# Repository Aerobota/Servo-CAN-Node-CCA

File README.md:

# Servo-CAN-Node-CCA
Circuit Card Assembly for Servo CAN Node

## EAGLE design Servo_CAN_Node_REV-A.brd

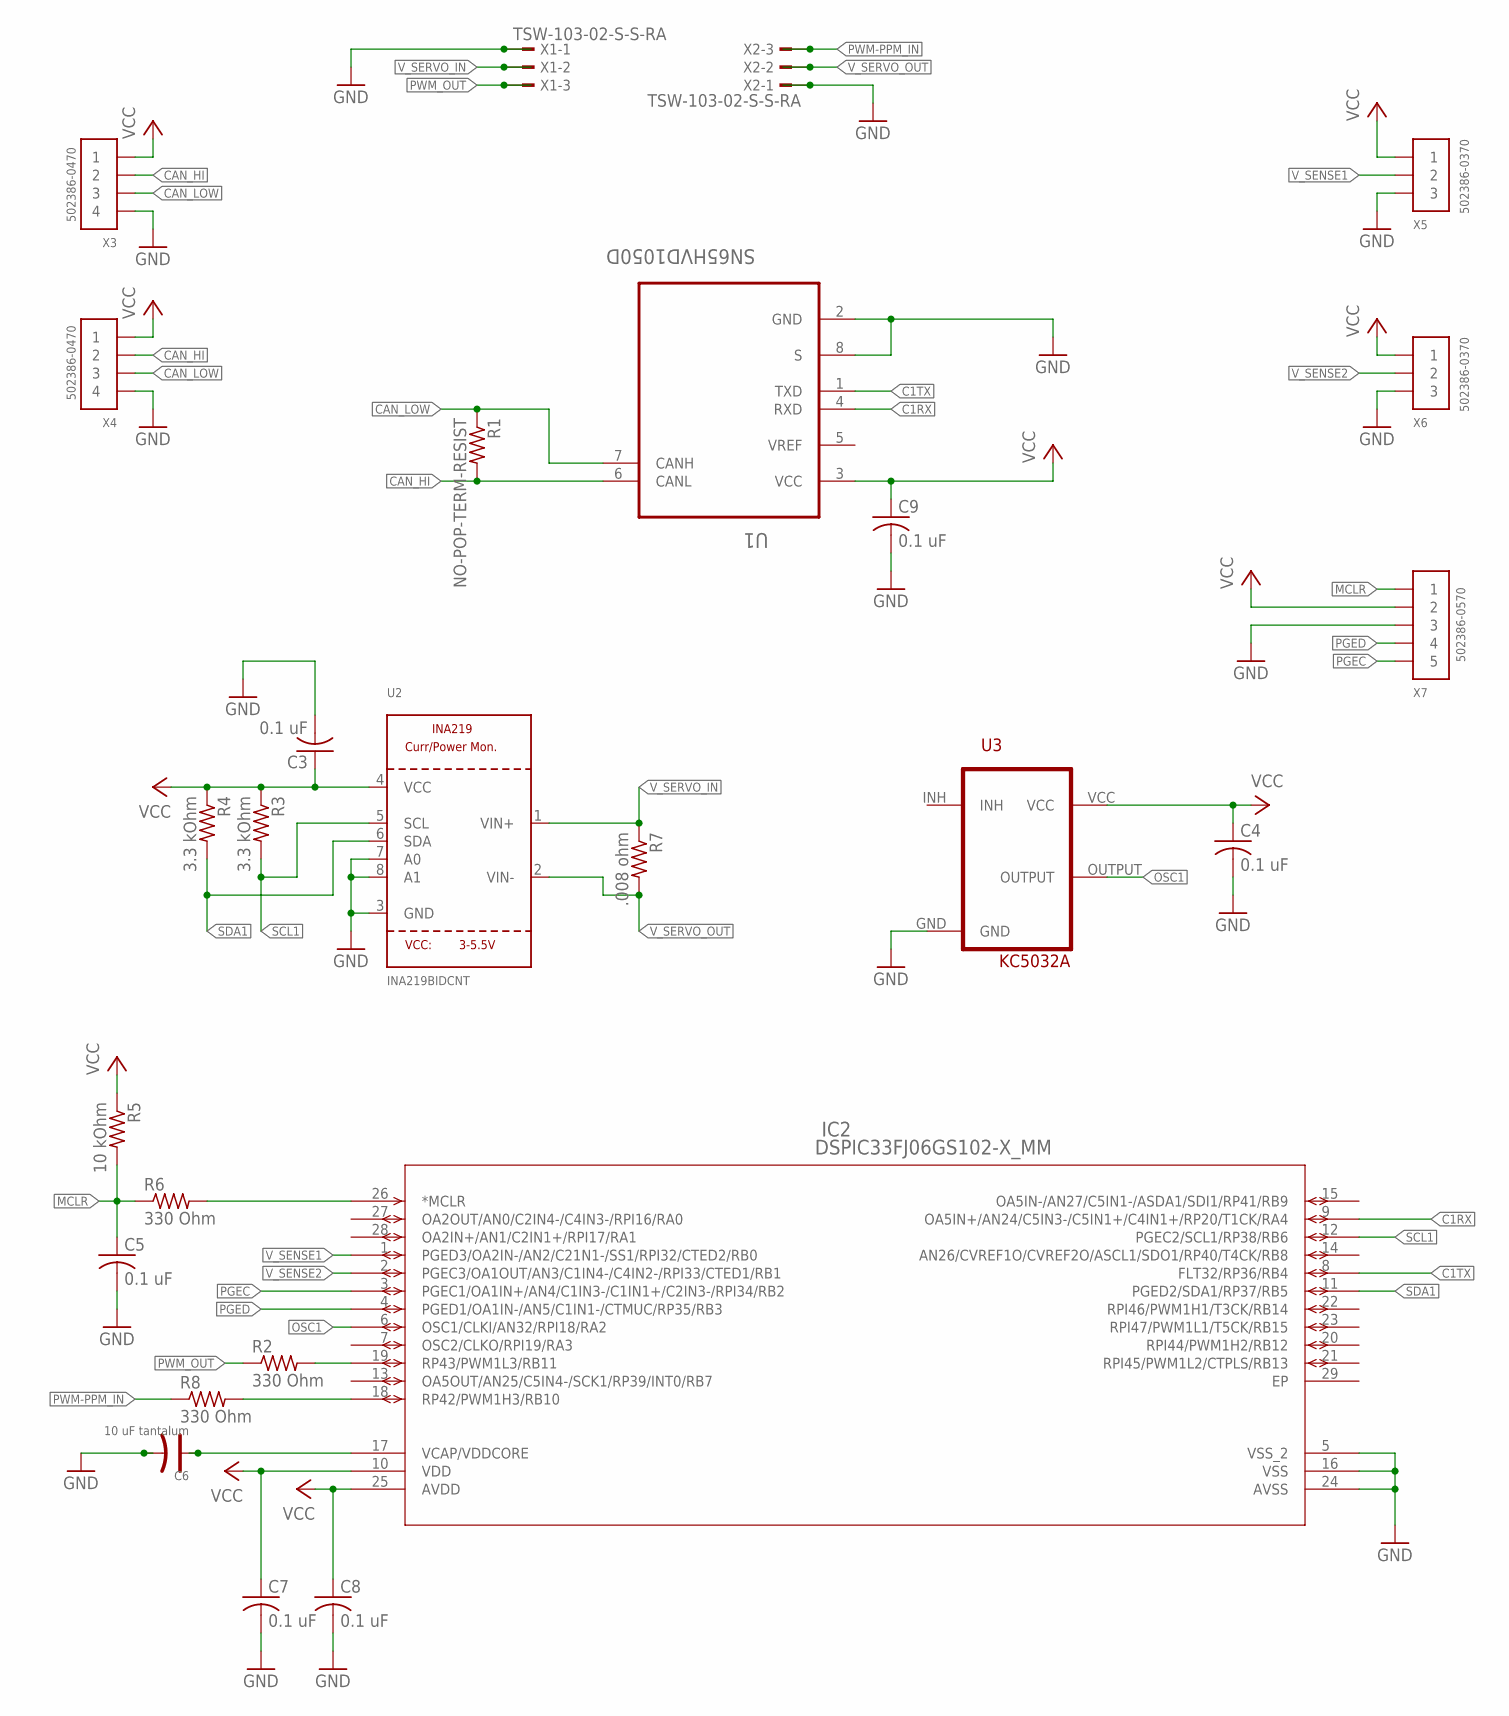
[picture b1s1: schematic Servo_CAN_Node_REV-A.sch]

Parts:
C3, C4, C5, C7, C8, C9: 0.1 uF; C0402
C6: 10 uF tantalum; AVX-A
IC2: DSPIC33FJ06GS102-X_MM; QFN-S28_6X6MC
R1: NO-POP-TERM-RESIST; R0402
R2, R6, R8: 330 Ohm; R0402
R3, R4: 3.3 kOhm; R0402
R5: 10 kOhm; R0402
R7: .008 ohm; R0805
U1: SN65HVD1050D; SOIC127P600X175-8N
U2: INA219BIDCNT; SOT23-8
U3: KC5032A
X1, X2: TSW-103-02-S-S-RA
X3, X4: CONN_4-1-502386; CM-502386-04
X5, X6: CONN_3-1-502386; CM-502386-03
X7: CONN_5-1-502386; CM-502386-05

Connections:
C1RX: IC2.9 (OA5IN+/AN24/C5IN3-/C5IN1+/C4IN1+/RP20/T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), U1.4 (RXD)
C1TX: IC2.8 (FLT32/RP36/RB4), U1.1 (TXD)
CAN_HI: R1.2, U1.6 (CANL), X3.2, X4.2
CAN_LOW: R1.1, U1.7 (CANH), X3.3, X4.3
GND: C3.2, C4.2, C5.2, C6.-, C7.2, C8.2, C9.2, IC2.5 (VSS_2), IC2.16 (VSS), IC2.24 (AVSS), U1.2 (GND), U1.8 (S), U2.3 (GND), U2.7 (A0), U2.8 (A1), U3.GND, X1.1, X2.1, X3.4, X4.4, X5.3, X6.3, X7.3
MCLR: C5.1, R5.2, R6.1, X7.1
MCLR_IC-SIDE: IC2.26 (*MCLR), R6.2
unnamed: C6.+, IC2.17 (VCAP/VDDCORE)
OSC1: IC2.6 (OSC1/CLKI/AN32/RPI18/RA2), U3.OUTPUT
PGEC: IC2.3 (PGEC1/OA1IN+/AN4/C1IN3-/C1IN1+/C2IN3-/R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), X7.5
PGED: IC2.4 (PGED1/OA1IN-/AN5/C1IN1-/CTMUC/RP35/RB3), X7.4
PWM-PPM_IN: R8.1, X2.3
PWM-PPM_IN_IC-SIDE: IC2.18 (RP42/PWM1H3/RB10), R8.2
PWM_OUT: R2.1, X1.3
PWM_OUT_IC-SIDE: IC2.19 (RP43/PWM1L3/RB11), R2.2
SCL1: IC2.12 (PGEC2/SCL1/RP38/RB6), R3.2, U2.5 (SCL)
SDA1: IC2.11 (PGED2/SDA1/RP37/RB5), R4.2, U2.6 (SDA)
VCC: C3.1, C4.1, C7.1, C8.1, C9.1, IC2.10 (VDD), IC2.25 (AVDD), R3.1, R4.1, R5.1, U1.3 (VCC), U2.4 (VCC), U3.VCC, X3.1, X4.1, X5.1, X6.1, X7.2
V_SENSE1: IC2.1 (PGED3/OA2IN-/AN2/C21N1-/SS1/RPI32/CTED2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), X5.2
V_SENSE2: IC2.2 (PGEC3/OA1OUT/AN3/C1IN4-/C4IN2-/RPI33/CT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), X6.2
V_SERVO_IN: R7.1, U2.1 (VIN+), X1.2
V_SERVO_OUT: R7.2, U2.2 (VIN-), X2.2

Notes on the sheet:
502386-0470
502386-0570
502386-0370

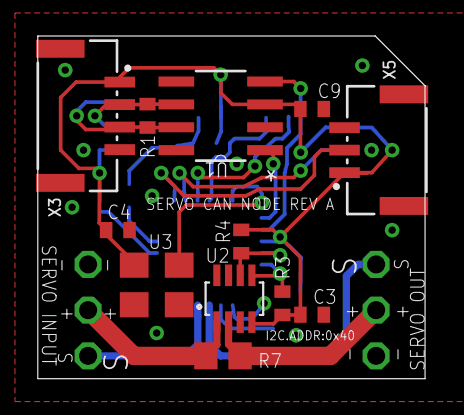
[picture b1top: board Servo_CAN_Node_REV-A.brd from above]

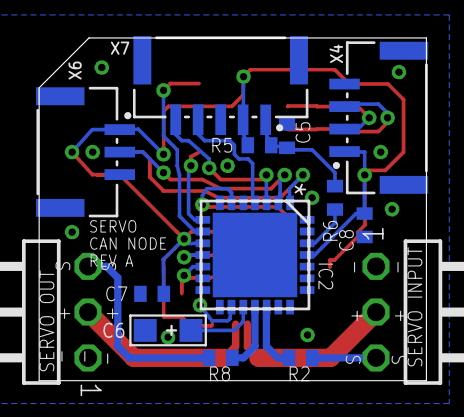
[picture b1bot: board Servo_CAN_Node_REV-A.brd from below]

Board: 2 copper layers, 21.5 x 19.0 mm, 26 parts (14 on the bottom side), 22 nets.

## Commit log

2015-05-01 Updated copyright holder.
